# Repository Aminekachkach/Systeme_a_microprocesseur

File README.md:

# Systeme_a_microprocesseur
This project was made by Me and my colleague Etienne PARMENTIER during our engineering studies at ENSEA.

BaudRate de l'USART2: 115200 Bits/ seconds

#TP 1.2 Questions
Q.13)
d'après la documentation technique la broche PB9 permet de permuter entre "flash program memory" et "system memory(bootloader)".
Il est important de tirer la broche en pull-down afin d'éviter qu'elle détecte un état haut au moment du reset et reflasher le mcu depuis le boot loader.

Q.14): La Bobine L1 et les capacités C5 et C7 forment un filtre de constante de temps T = 800 KHz.
Toutes les fréquences supérieures seront atténuées.

#TP 1.3 Questions
Q.3) On a les valeurs des capacités à la page 4, le schémas d'application à la page 1 permet d'être sûre que nos schémas correspondent.
Q.5) On a les valeurs des capacités à la page 25, avec le schémas qui correspond.
Q.6) La broche CS-barré est le chip select: quand elle est à l'état bas, la puce est active.
Q.7) La broche LDAC-barré synchonise le registre interne et la sortie du convertisseur.
Q.8) La broche MISO du STM32 n'est pas utilisé car aucune information n'est envoyé par le DAC au STM32. Le DAC fait juste des conversions,
Les données ne circule que dans un sens.
Q.10) Les Broches SWD sont standardisés.

#TP 1.4 Questions
Q.3) Les nombres 0805, 0603, 1206 sont les formats des boitiers des composants.
Q.4) LQFP signifie: Low Profile Quad Flat Package: La puce est basse (Low Profile), et plate (flat), et il y a des pins dans les 4 directions (Quad)
SOT-223 est un format de petit boitier pour transistor (Small Outline Transistor).
un SOIC (Small Outline Integrated Circuit) est une puce avec des pins de deux cotés, avec une épaisseur très faible.
-> Tout ces formats de puces sont montés en surface du PCB.

#TP 3.1 Questions
Q.2) Il y a beaucoup moins de fichiers générer, c'est parce-que l'on utilise des fonctions plus bas niveau sans les couches d'abstractions qu'il y a au
dessus.
Il y a beaucoup de fichiers avec __STATIC_INLINE

Q.4) __STATIC_INLINE est une macro qui contient les mots clés 'static' et 'inline'.
'static' indique au compilateur que la fonction n'est pas utilisé ailleurs que dans le fichier qui la contient.
la mise en ligne de fonction est une optimisation qui consiste à copier-coller le code de la fonction marqué 'inline'
à l'intérieur des fonctions qui l'appelle. Cela à plusieurs effets:
    - Les passe d'optimisation qui ont lieu après comme l'élimination du code mort, l'évaluation des constantes, etc... fonctionnent mieux.
    - Le code résultant est donc plus rapide, car on n'a plus besoin de sauvegarder l'état des registres dans la pile quand on appelle la fonction.
    - Dans certains cas, le code générer peut être plus gros, car les même instructions sont répétés plusieurs fois. Mais dans notre cas, les fonctions LL
    sont tellement petites que ça ne devrait pas poser de probléme. Si le compilateur calcule que plus d'instructions seront généré, il ne fera pas d'inlining.

Q.5) Le code est dans un fichier .h car du coup chaque 'compile unit' dois connaître la définition des fonctions à inliner, ce qui n'est pas nécéssaire
quand le code de chaque module est compilé séparement et qu'ils appellent des fonctions selon la convention d'appel standard du langage C.

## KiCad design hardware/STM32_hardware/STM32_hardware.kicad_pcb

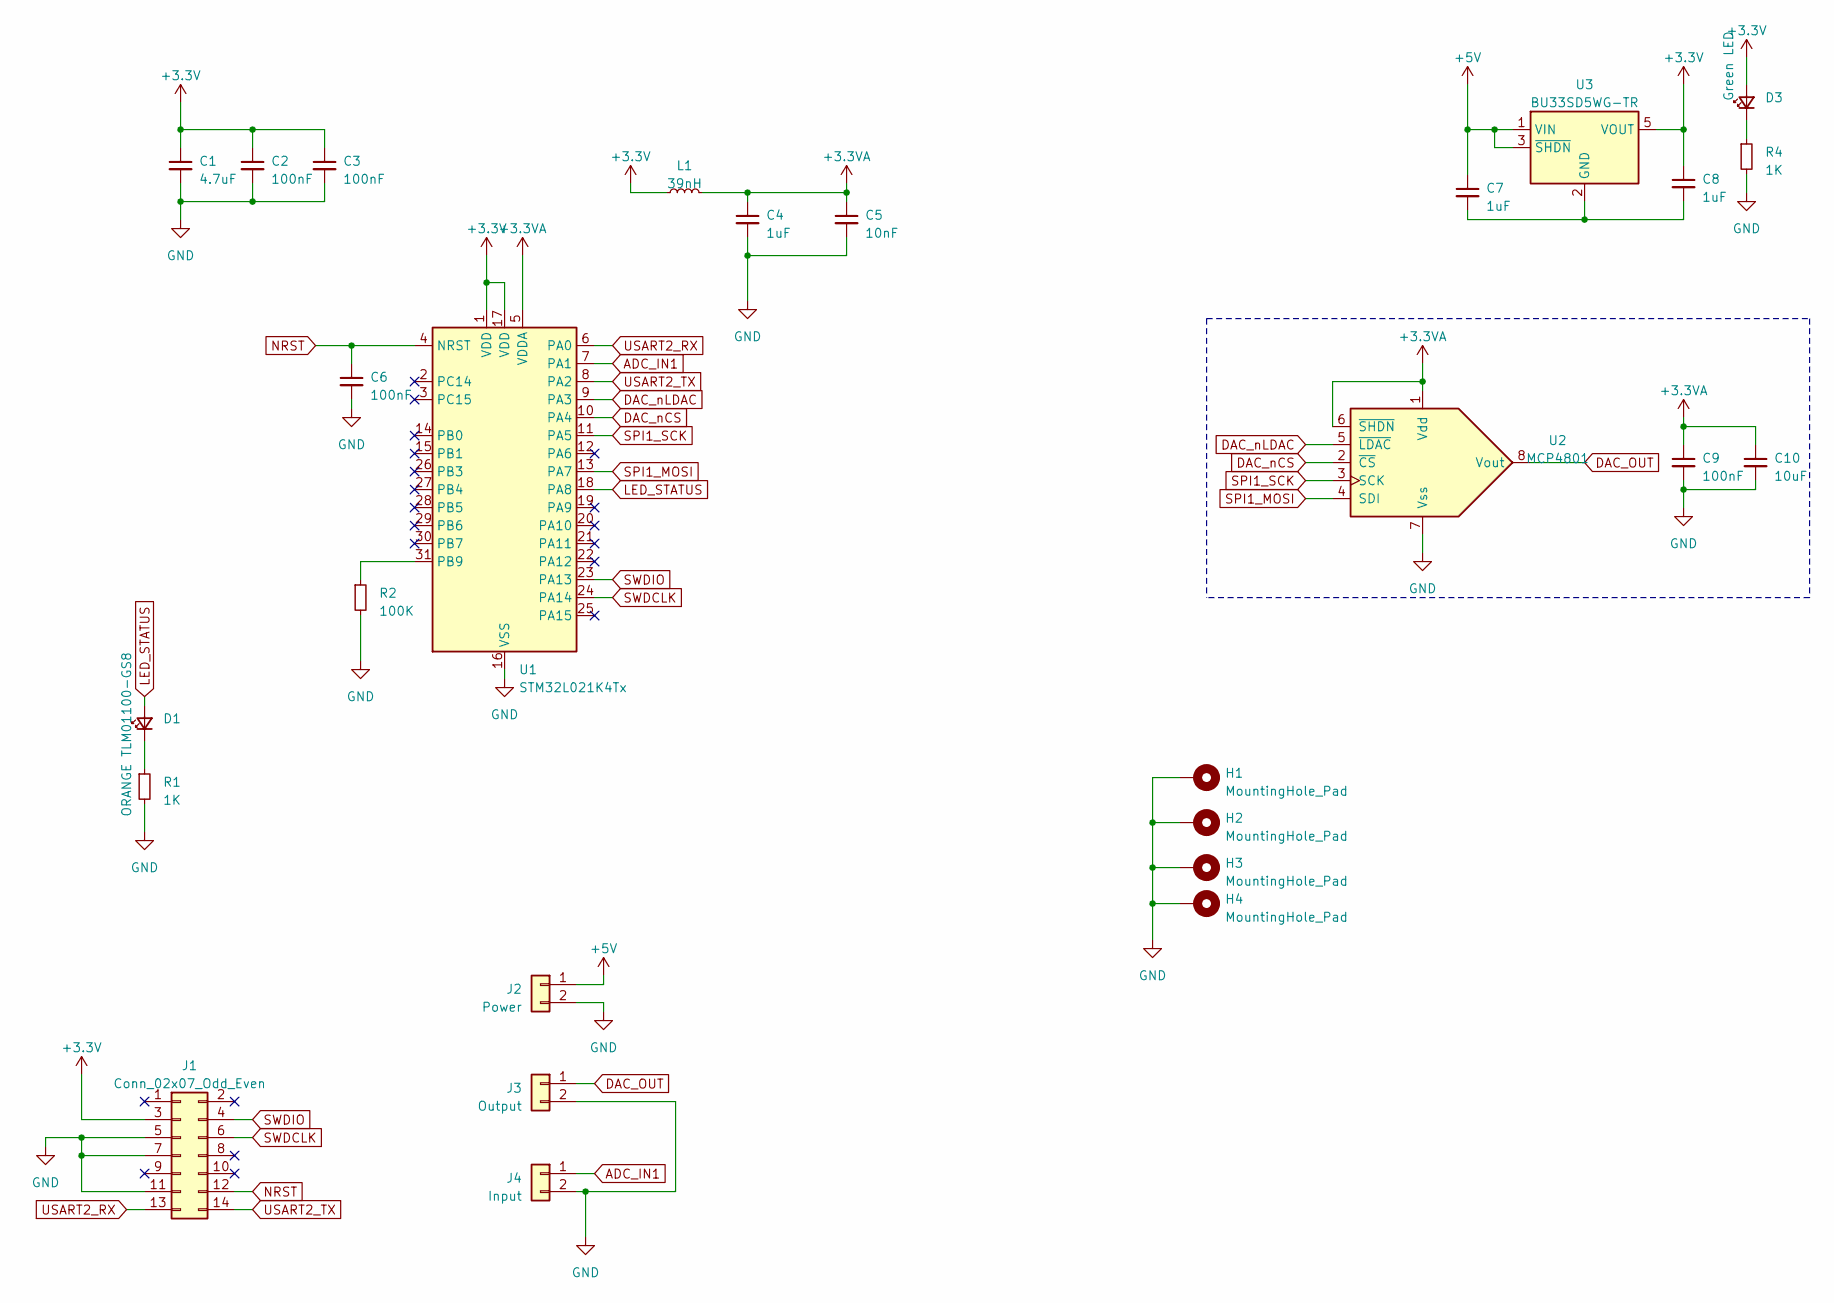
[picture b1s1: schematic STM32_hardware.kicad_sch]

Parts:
C1: 4.7uF; C_0805_2012Metric_Pad1.18x1.45mm_HandSolder
C2, C3, C6, C9: 100nF; C_0805_2012Metric_Pad1.18x1.45mm_HandSolder
C4, C7, C8: 1uF; C_0805_2012Metric_Pad1.18x1.45mm_HandSolder
C5: 10nF; C_0805_2012Metric_Pad1.18x1.45mm_HandSolder
C10: 10uF; C_0805_2012Metric_Pad1.18x1.45mm_HandSolder
D1: ORANGE TLM01100-GS8; LED_0603_1608Metric_Pad1.05x0.95mm_HandSolder
D3: Green LED; LED_0603_1608Metric_Pad1.05x0.95mm_HandSolder
H1, H2, H3, H4: MountingHole_Pad; MountingHole_3.2mm_M3_Pad
J1: Conn_02x07_Odd_Even; PinHeader_2x07_P1.27mm_Vertical_SMD
J2: Power; JST_XH_B2B-XH-A_1x02_P2.50mm_Vertical
J3: Output; JST_XH_B2B-XH-A_1x02_P2.50mm_Vertical
J4: Input; JST_XH_B2B-XH-A_1x02_P2.50mm_Vertical
L1: 39nH; L_0805_2012Metric_Pad1.05x1.20mm_HandSolder
R1, R4: 1K; R_0805_2012Metric_Pad1.20x1.40mm_HandSolder
R2: 100K; R_0805_2012Metric_Pad1.20x1.40mm_HandSolder
U1: STM32L021K4Tx; LQFP-32_7x7mm_P0.8mm
U2: MCP4801; SOIC-8_3.9x4.9mm_P1.27mm
U3: BU33SD5WG-TR; SOT-23-5

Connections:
+3.3V: C1.1, C2.1, C3.1, C8.1, D3.2 (A), J1.3, L1.1, U1.1 (VDD), U1.17 (VDD), U3.5 (VOUT)
+3.3VA: C4.1, C5.1, C9.1, C10.1, L1.2, U1.5 (VDDA), U2.1 (Vdd), U2.6 (~SHDN)
+5V: C7.1, J2.1, U3.1 (VIN), U3.3 (~SHDN)
ADC_IN1: J4.1, U1.7 (PA1)
DAC_OUT: J3.1, U2.8 (Vout)
DAC_nCS: U1.10 (PA4), U2.2 (~CS)
DAC_nLDAC: U1.9 (PA3), U2.5 (~LDAC)
GND: C1.2, C2.2, C3.2, C4.2, C5.2, C6.2, C9.2, C10.2, H1.1, H2.1, H3.1, H4.1, J1.5, J1.7, J1.11, J2.2, J3.2, J4.2, R1.2, R2.2, R4.2, U1.16 (VSS), U1.32 (VSS), U2.7 (Vss)
LED_STATUS: D1.2 (A), U1.18 (PA8)
NRST: C6.1, J1.12, U1.4 (NRST)
unnamed: D1.1 (K), R1.1
unnamed: D3.1 (K), R4.1
unnamed: R2.1, U1.31 (PB9)
unnamed: C7.2, C8.2, U3.2 (GND)
SPI1_MOSI: U1.13 (PA7), U2.4 (SDI)
SPI1_SCK: U1.11 (PA5), U2.3 (SCK)
SWDCLK: J1.6, U1.24 (PA14)
SWDIO: J1.4, U1.23 (PA13)
USART2_RX: J1.13, U1.6 (PA0)
USART2_TX: J1.14, U1.8 (PA2)

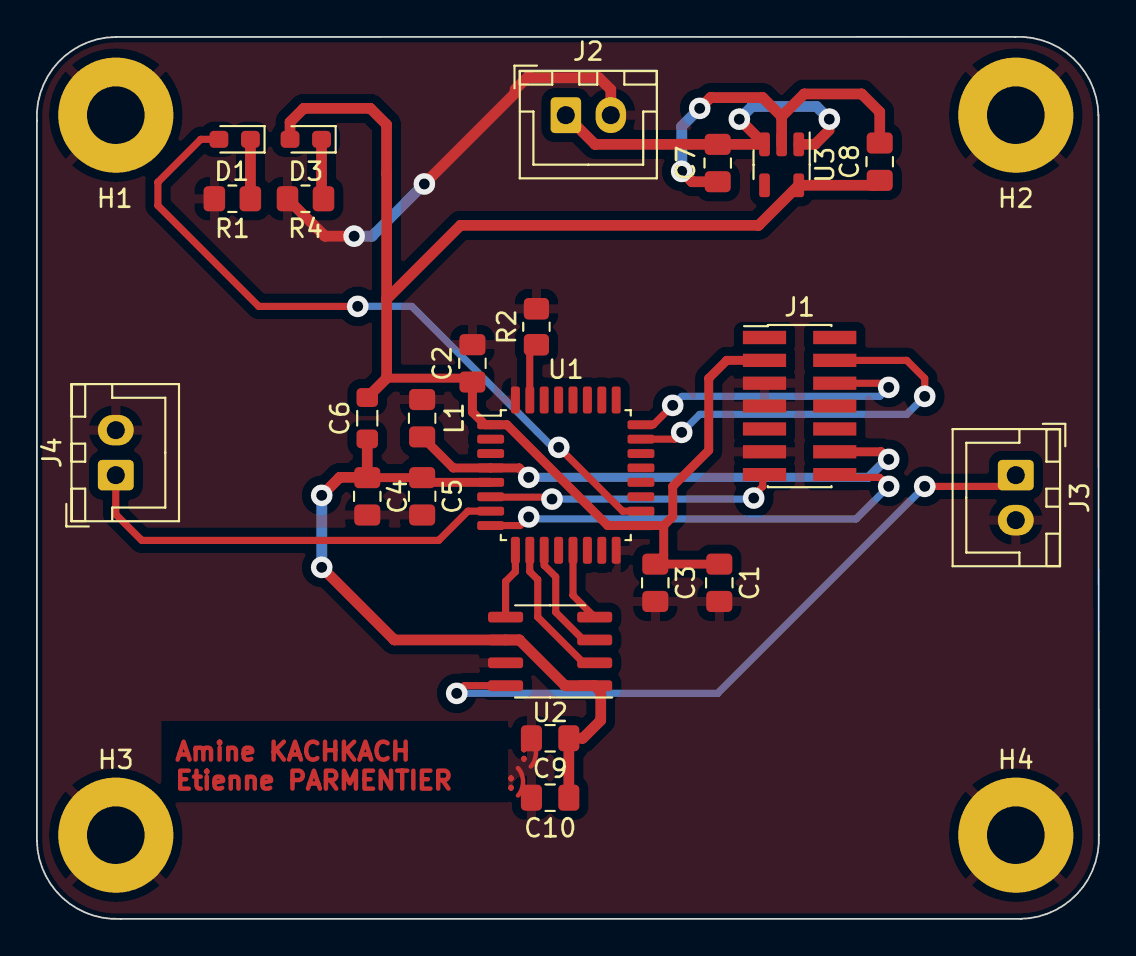
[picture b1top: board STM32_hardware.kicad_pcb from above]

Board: 2 copper layers, 59.0 x 49.0 mm, 27 parts (0 on the bottom side), 20 nets.

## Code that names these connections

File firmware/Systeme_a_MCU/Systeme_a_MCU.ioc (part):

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Mcu.Name=STM32L021K4Tx
Mcu.Package=LQFP32
Mcu.UserName=STM32L021K4Tx
PA0-CK_IN.Mode=Asynchronous
PA0-CK_IN.Signal=USART2_RX
PA1.Mode=IN1
PA1.Signal=ADC_IN1
PA13.Mode=Serial_Wire
PA13.Signal=SYS_SWDIO
PA14.Mode=Serial_Wire
PA14.Signal=SYS_SWCLK
PA2.Mode=Asynchronous
PA2.Signal=USART2_TX
PA3.GPIOParameters=GPIO_Label
PA3.GPIO_Label=DAC_nLDAC
PA3.Signal=GPIO_Output
PA4.GPIOParameters=GPIO_Label
PA4.GPIO_Label=DAC_nCS
PA4.Signal=GPIO_Output
PA5.Mode=TX_Only_Simplex_Unidirect_Master
PA5.Signal=SPI1_SCK
PA7.Mode=TX_Only_Simplex_Unidirect_Master
PA7.Signal=SPI1_MOSI
PA8.Signal=S_TIM2_CH1
RCC.HSE_VALUE=8000000
RCC.SYSCLKFreq_VALUE=32000000
RCC.SYSCLKSource=RCC_SYSCLKSOURCE_PLLCLK
board=custom

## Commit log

2023-02-15 second
2023-02-15 Second Commit for testing
2023-02-15 DataSheet of Microprocessor
2023-02-15 Auto-Generated firmware setup
2023-02-15 Fully Configured pinout
2023-02-15 hardware
2023-02-15 Renamed and discarded dupliacte directories
2023-02-15 Readme
2023-02-15 Added answer to question 14
2023-02-15 Correction de la question 14
2023-02-15 Add LDO datasheet
2023-02-15 Question 1.3.3
2023-02-15 Answer to question 1.3.5
2023-02-15 Various 1.3.x answers
2023-02-15 answers to 1.3.9
2023-02-15 schema de principe
2023-02-15 Finished Question of TP 1
2023-02-16 harware_PCB_contour
2023-02-16 Hardware_routin
2023-02-16 GERBER_included
2023-02-16 Hardware_routing
2023-02-16 Hardware_routing_emoji
2023-03-10 Replaced HAL Drivers with Low Level Drivers
2023-03-10 Added cubeIde project
2023-03-10 Begin Firmware writing
